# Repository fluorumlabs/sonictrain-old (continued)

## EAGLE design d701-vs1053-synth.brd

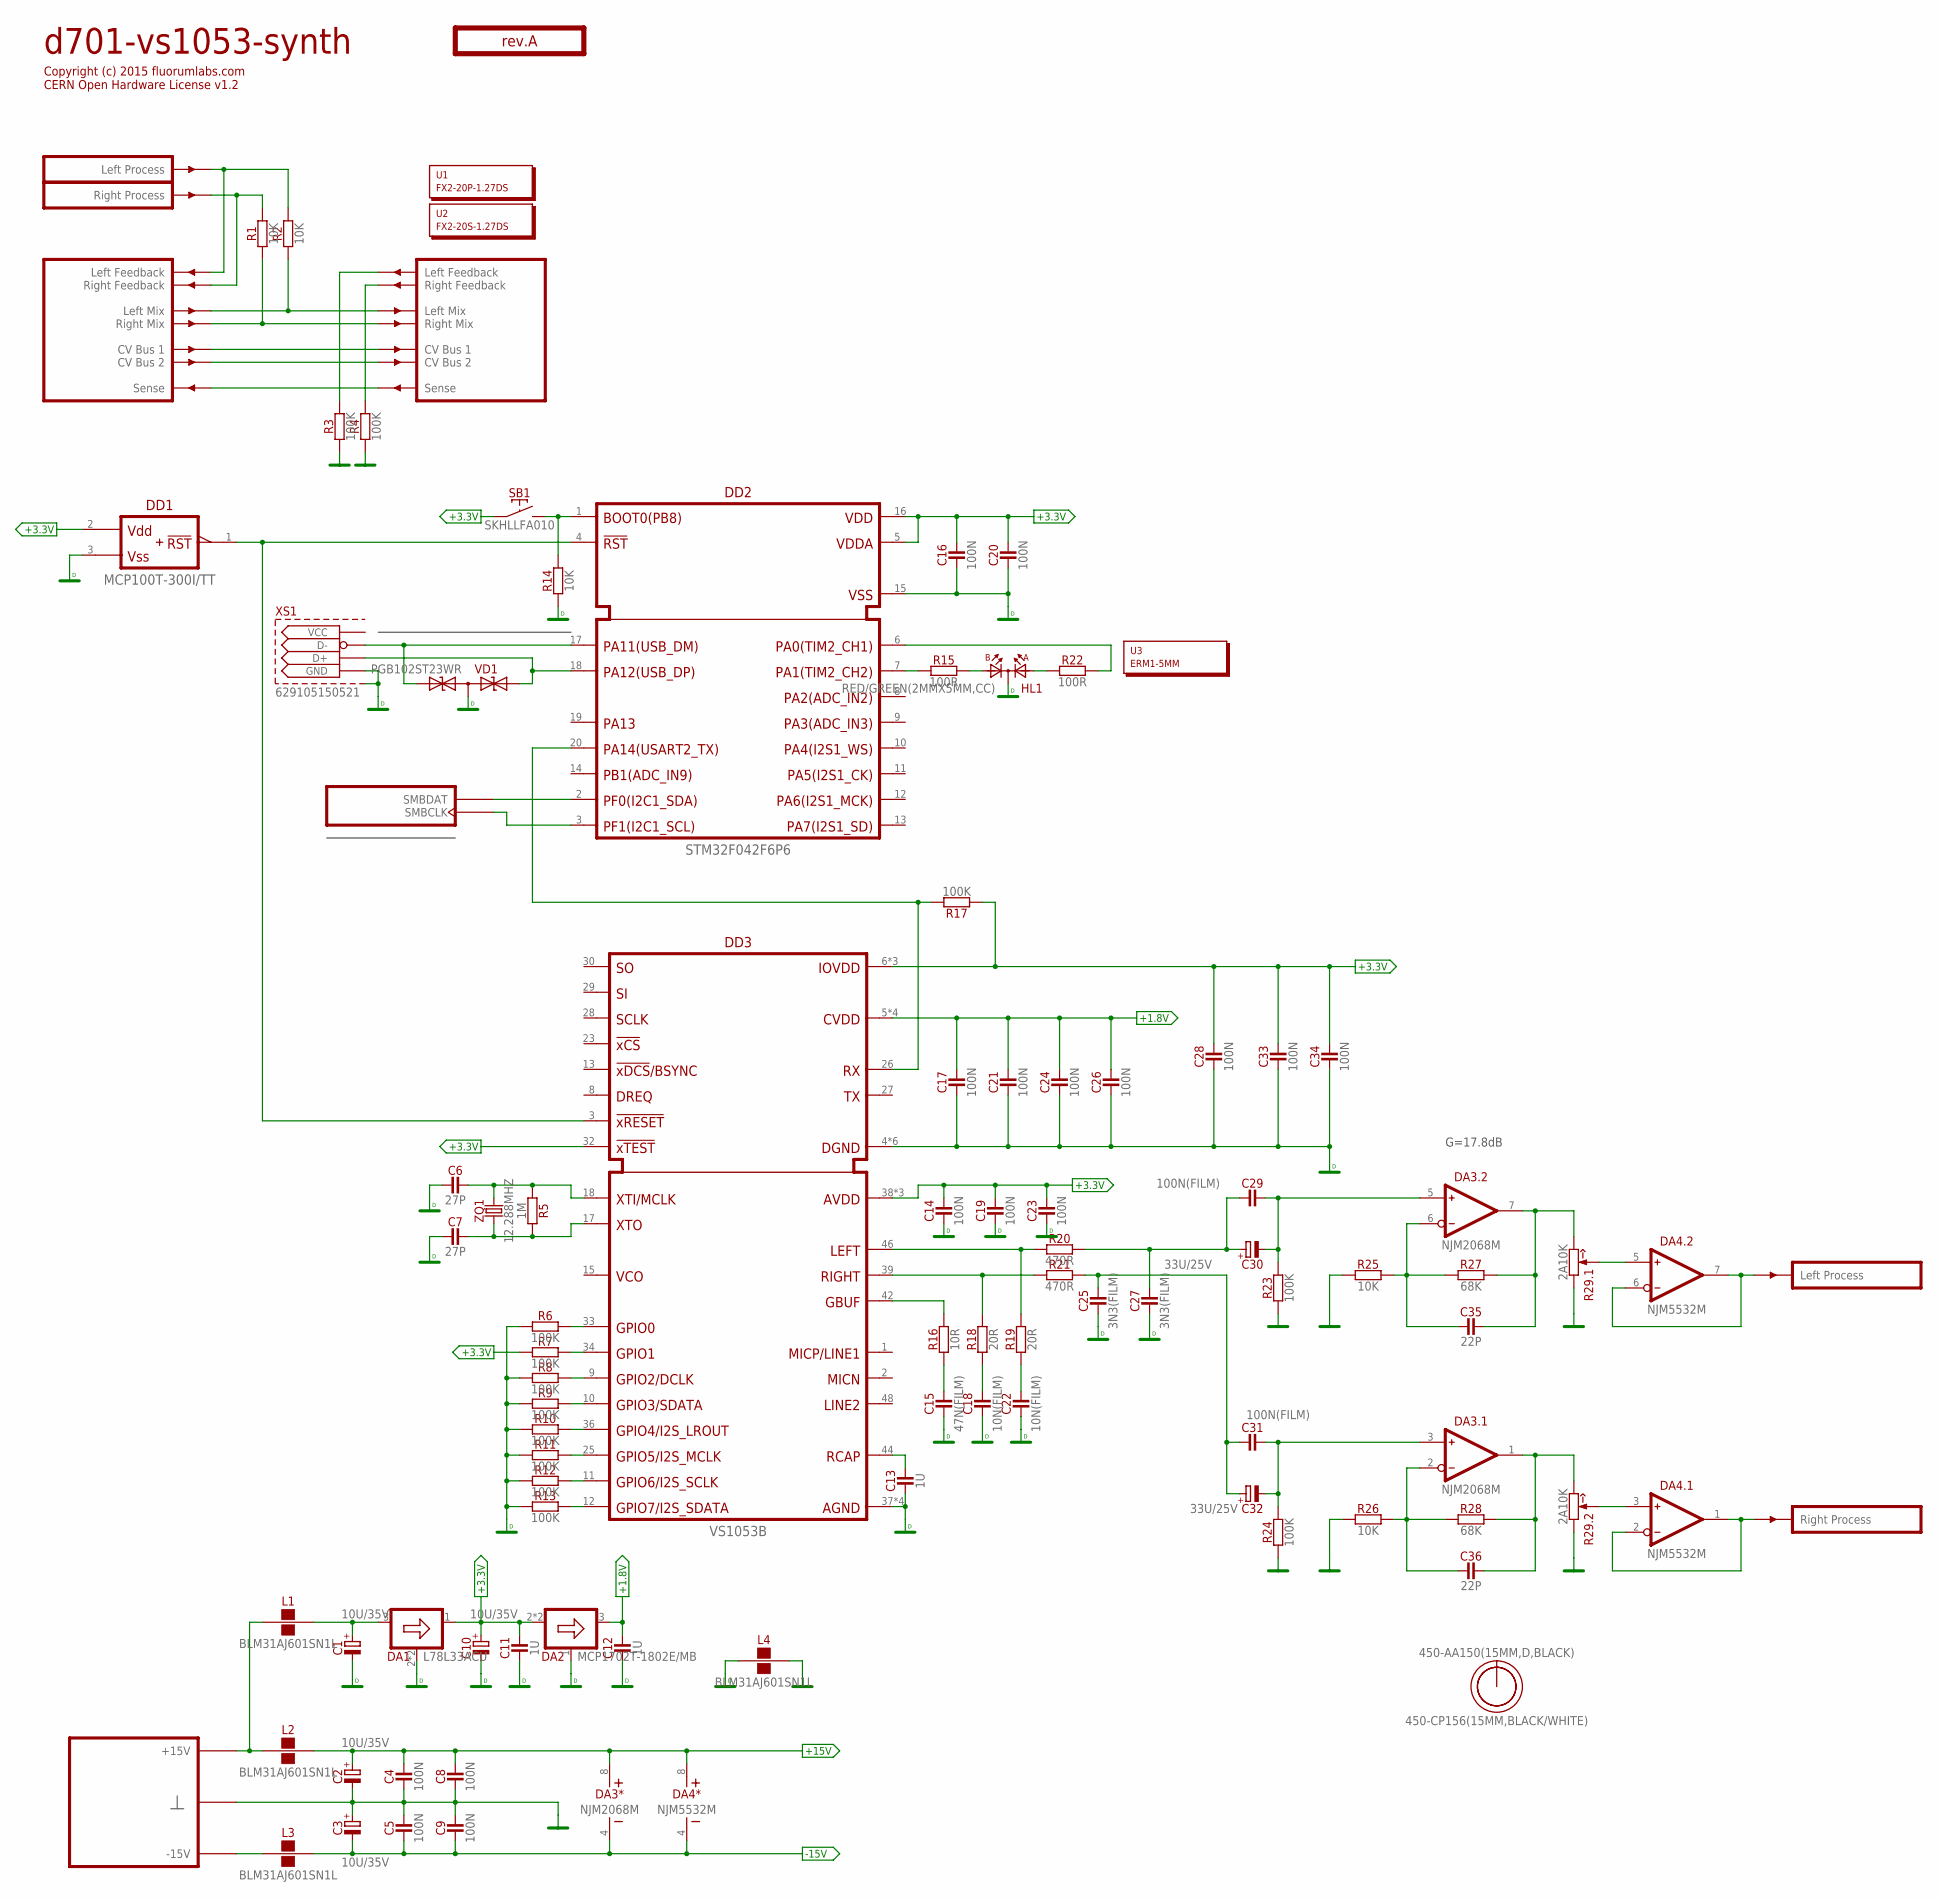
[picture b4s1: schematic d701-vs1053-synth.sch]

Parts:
C1, C2, C3, C10: 10U/35V; E2-5
C4, C5, C8, C9, C14, C16, C17, C19, C20, C21, C23, C24, C26, C28, C33, C34: 100N; C-0805
C6, C7: 27P; C-0805
C11, C12, C13: 1U; C-0805
C15: 47N(FILM); C050-025X075
C18, C22: 10N(FILM); C050-025X075
C25, C27: 3N3(FILM); C050-025X075
C29, C31: 100N(FILM); C050-025X075
C30, C32: 33U/25V; E2,5-7
C35, C36: 22P; C-0805
DA1: L78L33ACU; SOT89
DA2: MCP1702T-1802E/MB; SOT89
DA3: NJM2068M; SO-8
DA4: NJM5532M; SO-8
DD1: MCP100T-300I/TT; SOT23
DD2: STM32F042F6P6; TSSOP20
DD3: VS1053B; LQFP48-7X7
HL1: RED/GREEN(2MMX5MM,CC); LED2X5-3PIN
L1, L2, L3, L4: BLM31AJ601SN1L; 1206
O1: TITLE; EMPTY
O2: 450-AA150(15MM,D,BLACK); EMPTY
O3: 450-CP156(15MM,BLACK/WHITE); EMPTY
PCB1: rev.A; ST2-BOARD-50
R1, R2, R14, R25, R26: 10K; R-0805
R3, R4, R6, R7, R8, R9, R10, R11, R12, R13, R17, R23, R24: 100K; R-0805
R5: 1M; R-0805
R15, R22: 100R; R-0805
R16: 10R; R-0805
R18, R19: 20R; R-0805
R20, R21: 470R; R-0805
R27, R28: 68K; R-0805
R29: 2A10K; RV11-DUAL
SB1: SKHLLFA010
U1: FX2-20P-1.27DS; EMPTY
U2: FX2-20S-1.27DS; EMPTY
U3: ERM1-5MM; EMPTY
VD1: PGB102ST23WR; SOT23
XS1: 629105150521; MICROUSB-WURTH
ZQ1: 12.288MHZ; 3225

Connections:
+1.8V: C12.2, C17.2, C21.2, C24.2, C26.2, DA2.3 (OUT), DD3.5 (CVDD), DD3.7 (CVDD), DD3.24 (CVDD), DD3.31 (CVDD)
+3.3V: C10.+, C11.2, C14.2, C16.2, C19.2, C20.2, C23.2, C28.2, C33.2, C34.2, DA1.1 (OUT), DA2.2 (IN), DA2.2@1 (IN), DD1.2 (VDD), DD2.5 (VDDA), DD2.16 (VDD), DD3.6 (IOVDD), DD3.14 (IOVDD), DD3.19 (IOVDD), DD3.32 (!XTEST), DD3.38 (AVDD), DD3.43 (AVDD), DD3.45 (AVDD), R7.1, R17.1, SB1.1
+15V: C2.+, C4.2, C8.2, DA3.8 (V+), DA4.8 (V+), L2.2
-15V: C3.-, C5.1, C9.1, DA3.4 (V-), DA4.4 (V-), L3.2
DGND: C1.-, C6.1, C7.1, C10.-, C11.1, C12.1, C13.1, C14.1, C15.1, C16.1, C17.1, C18.1, C19.1, C20.1, C21.1, C22.1, C23.1, C24.1, C25.1, C26.1, C27.1, C28.1, C33.1, C34.1, DA1.2 (GND), DA1.2@1 (GND), DA2.1 (GND), DD1.3 (VSS), DD2.15 (VSS), DD3.4 (DGND), DD3.16 (DGND), DD3.20 (DGND), DD3.21 (DGND), DD3.22 (DGND), DD3.35 (DGND), DD3.37 (AGND), DD3.40 (AGND), DD3.41 (AGND), DD3.47 (AGND), HL1.K, L4.1, R6.1, R8.1, R9.1, R10.1, R11.1, R12.1, R13.1, R14.1, VD1.3 (C), XS1.5 (GND), XS1.S1, XS1.S2 (S1), XS1.S3 (S1), XS1.S4 (S1), XS1.S5 (S1), XS1.S6 (S1)
GND: C2.-, C3.+, C4.1, C5.2, C8.1, C9.2, L4.2, PCB1.B4 (GND), PCB1.B4' (GND), PCB1.B5 (GND), PCB1.B5' (GND), PCB1.B6 (GND), PCB1.B6' (GND), PCB1.B7 (GND), PCB1.B7' (GND), PCB1.B8 (GND), PCB1.B8' (GND), R3.1, R4.1, R23.1, R24.1, R25.1, R26.1, R29.1 (CCW), R29.1' (CCW)
LMIX: PCB1.ALMIX (LMIX), PCB1.ALMIX' (LMIX'), R2.1
unnamed: L1.1, L2.1, PCB1.A+15 (P+15V), PCB1.A+15' (P+15V), PCB1.B+15 (P+15V), PCB1.B+15' (P+15V)
unnamed: PCB1.ARFBK' (RFBK'), R4.2
unnamed: PCB1.ALFBK' (LFBK'), R3.2
unnamed: L3.1, PCB1.A-15 (P-15V), PCB1.A-15' (P-15V), PCB1.B-15 (P-15V), PCB1.B-15' (P-15V)
unnamed: C27.2, C29.1, C30.+, R20.2
unnamed: C31.2, C32.-, DA3.3 (IN+), R24.2
unnamed: C29.2, C30.-, DA3.5 (IN+), R23.2
unnamed: C36.2, DA3.1 (OUT), R28.2, R29.3' (CW)
unnamed: C35.2, DA3.7 (OUT), R27.2, R29.3 (CW)
unnamed: C35.1, DA3.6 (IN-), R25.2, R27.1
unnamed: C36.1, DA3.2 (IN-), R26.2, R28.1
unnamed: PCB1.BSENSE (SENSE), PCB1.BSENSE' (SENSE')
unnamed: C7.2, DD3.17 (XTO), R5.2, ZQ1.1
unnamed: DA4.6 (IN-), DA4.7 (OUT), PCB1.BOUTL' (OUTL)
unnamed: DA4.1 (OUT), DA4.2 (IN-), PCB1.BOUTR' (OUTR)
unnamed: DA4.5 (IN+), R29.2 (W)
unnamed: DA4.3 (IN+), R29.2' (W)
unnamed: C1.+, DA1.3 (IN), L1.2
unnamed: C6.2, DD3.18 (XTI/MCLK), R5.1, ZQ1.3 (2)
unnamed: C25.2, C31.1, C32.+, R21.2
unnamed: PCB1.ARFBK (RFBK), PCB1.BINR (INR), R1.2
unnamed: PCB1.ALFBK (LFBK), PCB1.BINL (INL), R2.2
unnamed: PCB1.ACV1 (CV1), PCB1.ACV1' (CV1')
unnamed: PCB1.ACV2 (CV2), PCB1.ACV2' (CV2')
unnamed: DD1.1 (!RST), DD2.4 (!RST), DD3.3 (!XRESET)
unnamed: DD3.12 (GPIO7/I2S_SDATA), R13.2
unnamed: DD3.11 (GPIO6/I2S_SCLK), R12.2
unnamed: DD3.25 (GPIO5/I2S_MCLK), R11.2
unnamed: DD2.20 (PA14), DD3.26 (RX), R17.2
unnamed: DD3.36 (GPIO4/I2S_LROUT), R10.2
unnamed: DD3.10 (GPIO3/SDATA), R9.2
unnamed: DD3.9 (GPIO2/DCLK), R8.2
unnamed: DD3.34 (GPIO1), R7.2
unnamed: DD3.33 (GPIO0), R6.2
unnamed: C13.2, DD3.44 (RCAP)
unnamed: DD2.7 (PA1), R15.1
unnamed: C15.2, R16.1
unnamed: HL1.A2, R15.2
unnamed: DD3.42 (GBUF), R16.2
unnamed: DD3.39 (RIGHT), R18.2, R21.1
unnamed: C18.2, R18.1
unnamed: DD3.46 (LEFT), R19.2, R20.1
unnamed: C22.2, R19.1
unnamed: HL1.A1, R22.1
unnamed: DD2.6 (PA0), R22.2
unnamed: DD2.1 (BOOT0), R14.2, SB1.2
RMIX: PCB1.ARMIX (RMIX), PCB1.ARMIX' (RMIX'), R1.1
SMBCLK: DD2.3 (PF1), PCB1.ASMBCLK (SMBCLK), PCB1.ASMBCLK' (SMBCLK)
SMBDAT: DD2.2 (PF0), PCB1.ASMBDAT (SMBDAT), PCB1.ASMBDAT' (SMBDAT)
USB_N: DD2.17 (PA11), VD1.2 (A1), XS1.2 (D-)
USB_P: DD2.18 (PA12), VD1.1 (A), XS1.3 (D+)

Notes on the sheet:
G=17.8dB

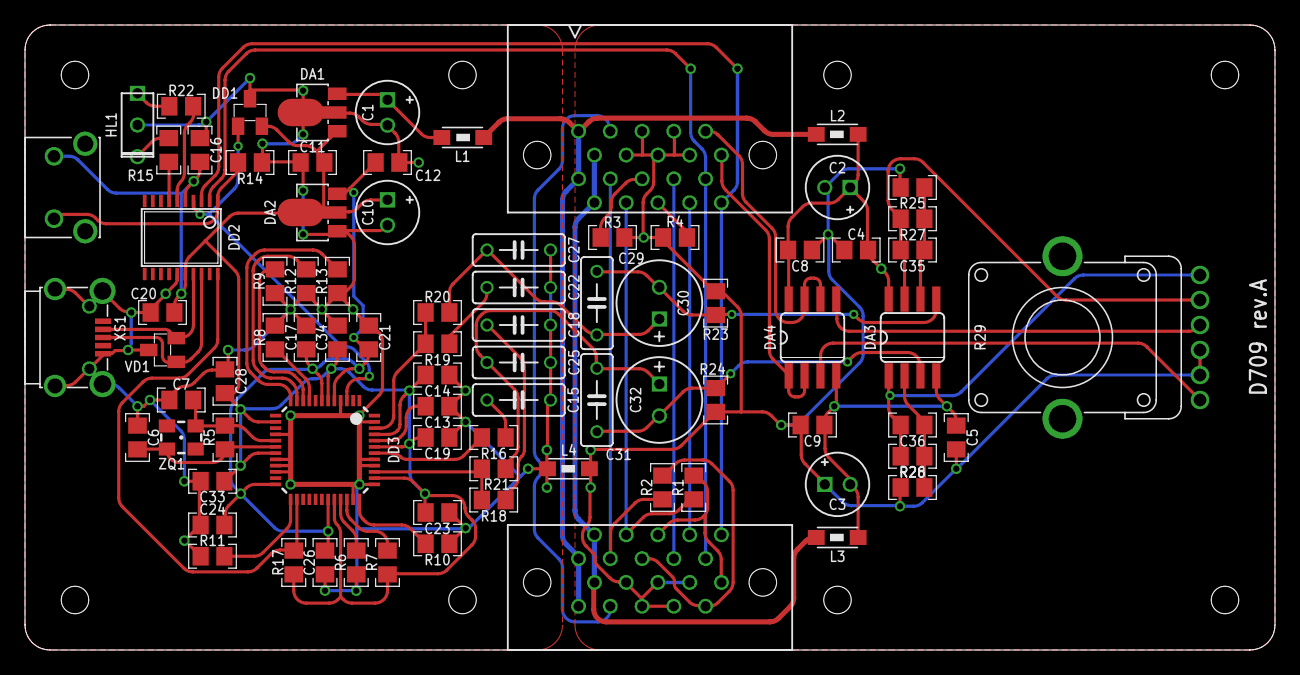
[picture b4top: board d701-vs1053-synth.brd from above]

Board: 2 copper layers, 100.0 x 50.0 mm, 95 parts (0 on the bottom side), 58 nets.

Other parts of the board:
U4, U5, U6, U7: SCREW-M2X8; EMPTY
U8, U9, U10, U11: NUT-M2-SELFLOCK; EMPTY

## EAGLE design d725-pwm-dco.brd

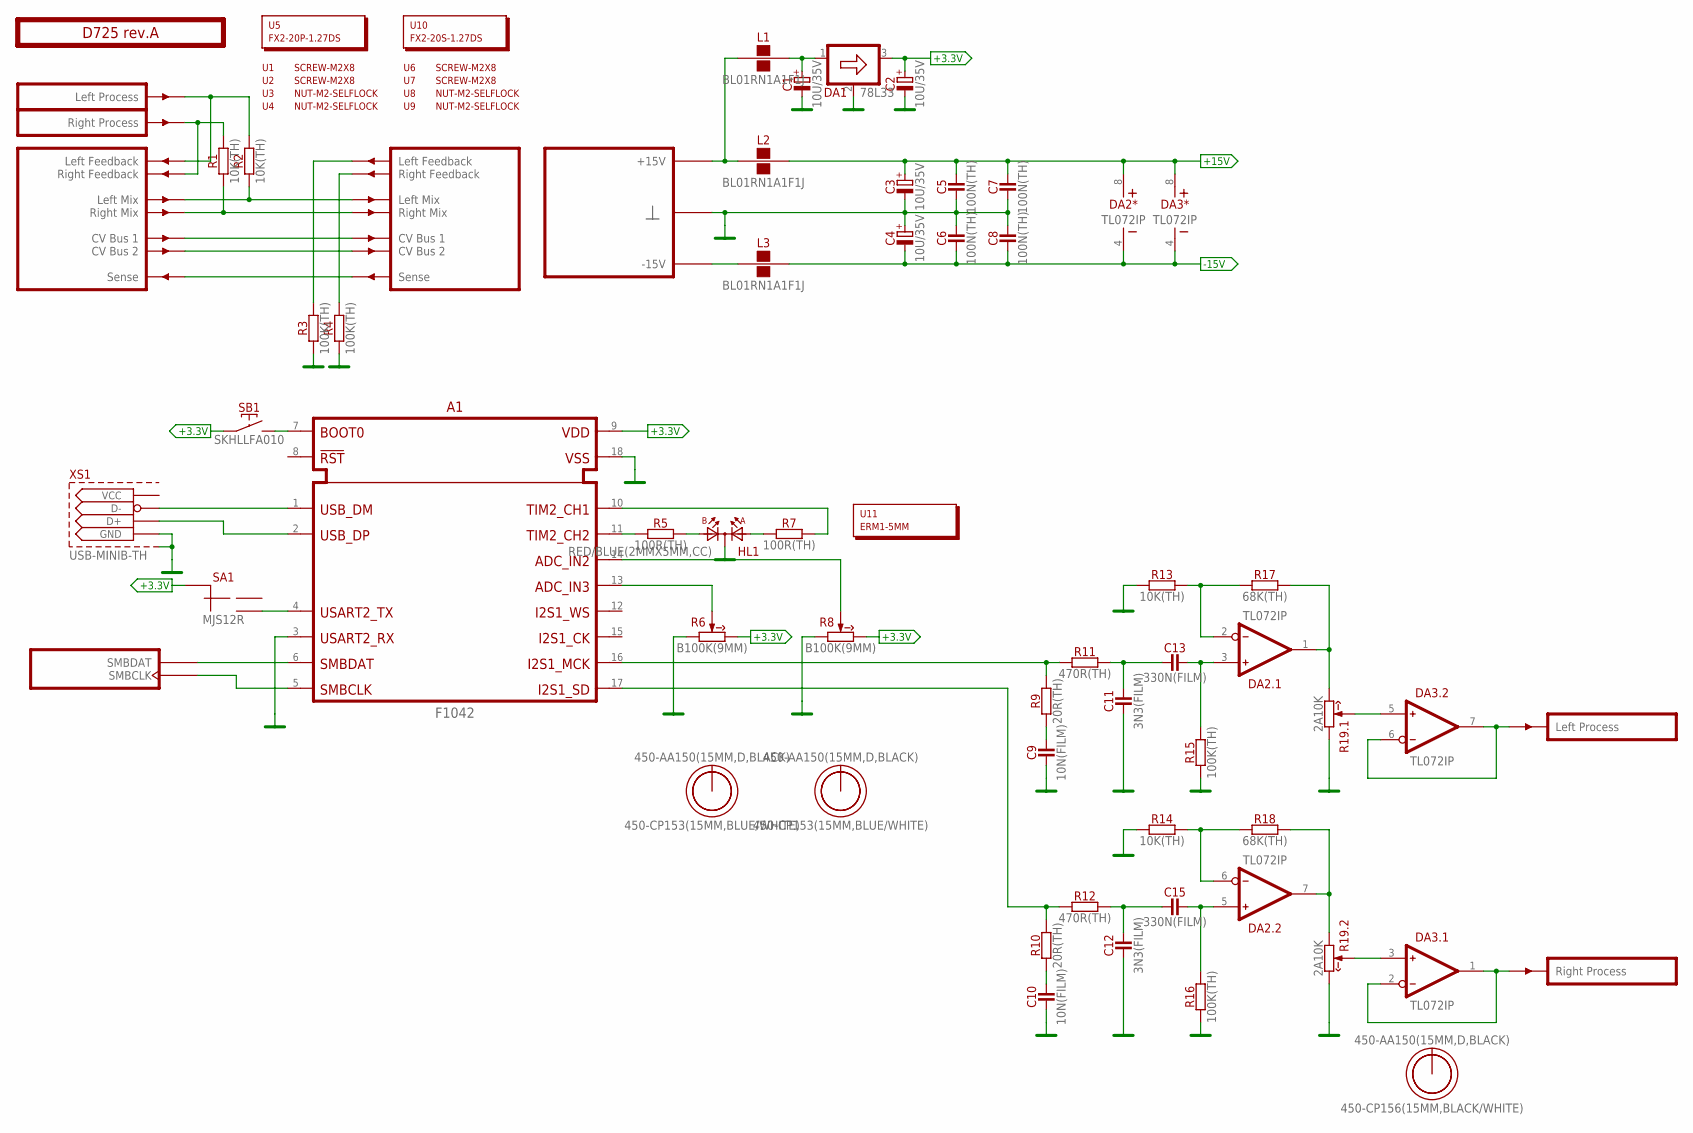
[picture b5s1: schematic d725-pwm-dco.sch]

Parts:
A1: F1042; F-DIP18
C1, C2, C3, C4: 10U/35V; E2-5
C5, C6, C7, C8: 100N(TH); C050-024X044
C9, C10: 10N(FILM); C050-025X075
C11, C12: 3N3(FILM); C050-025X075
C13, C15: 330N(FILM); C050-035X075
DA1: 78L33; TO92
DA2, DA3: TL072IP; DIP-8
HL1: RED/BLUE(2MMX5MM,CC); LED2X5-3PIN
L1, L2, L3: BL01RN1A1F1J; BL01RN1A
O1, O3, O5: 450-AA150(15MM,D,BLACK); EMPTY
O2, O4: 450-CP153(15MM,BLUE/WHITE); EMPTY
O6: 450-CP156(15MM,BLACK/WHITE); EMPTY
PCB1: D725 rev.A; ST2-BOARD-50
R1, R2, R13, R14: 10K(TH); R-0207/10
R3, R4, R15, R16: 100K(TH); R-0207/10
R5, R7: 100R(TH); R-0207/10
R6, R8: B100K(9MM); RV09-SINGLE
R9, R10: 20R(TH); R-0207/10
R11, R12: 470R(TH); R-0207/10
R17, R18: 68K(TH); R-0207/10
R19: 2A10K; RV11-DUAL
SA1: MJS12R; APEM-MJS12R
SB1: SKHLLFA010
U1, U2, U6, U7: SCREW-M2X8; EMPTY
U3, U4, U8, U9: NUT-M2-SELFLOCK; EMPTY
U5: FX2-20P-1.27DS; EMPTY
U10: FX2-20S-1.27DS; EMPTY
U11: ERM1-5MM; EMPTY
XS1: USB-MINIB-TH; USB-MB-H

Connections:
+3.3V: A1.9 (VDD), C2.+, DA1.3 (OUT), R6.3 (CW), R8.3 (CW), SA1.C (CM), SB1.1
+15V: C3.+, C5.2, C7.2, DA2.8 (V+), DA3.8 (V+), L2.2
-15V: C4.-, C6.1, C8.1, DA2.4 (V-), DA3.4 (V-), L3.2
GND: A1.3 (USART2_RX), A1.18 (VSS), C1.-, C2.-, C3.-, C4.+, C5.1, C6.2, C7.1, C8.2, C9.1, C10.1, C11.1, C12.1, DA1.2 (GND), HL1.K, PCB1.B4 (GND), PCB1.B4' (GND), PCB1.B5 (GND), PCB1.B5' (GND), PCB1.B6 (GND), PCB1.B6' (GND), PCB1.B7 (GND), PCB1.B7' (GND), PCB1.B8 (GND), PCB1.B8' (GND), R3.1, R4.1, R6.1 (CCW), R8.1 (CCW), R13.1, R14.1, R15.1, R16.1, R19.1 (CCW), R19.3' (CW), XS1.GND, XS1.P$1 (S1), XS1.P$2 (S1), XS1.P$6 (S1), XS1.P$7 (S1)
LMIX: PCB1.ALMIX (LMIX), PCB1.ALMIX' (LMIX'), R2.1
unnamed: L1.1, L2.1, PCB1.A+15 (P+15V), PCB1.A+15' (P+15V), PCB1.B+15 (P+15V), PCB1.B+15' (P+15V)
unnamed: PCB1.ARFBK (RFBK), PCB1.BINR (INR), R1.2
unnamed: C1.+, DA1.1 (IN), L1.2
unnamed: PCB1.ALFBK (LFBK), PCB1.BINL (INL), R2.2
unnamed: A1.11 (TIM2_CH2), R5.1
unnamed: A1.6 (SBMDAT), PCB1.ASMBDAT (SMBDAT), PCB1.ASMBDAT' (SMBDAT)
unnamed: A1.5 (SMBCLK), PCB1.ASMBCLK (SMBCLK), PCB1.ASMBCLK' (SMBCLK)
unnamed: A1.7 (BOOT0), SB1.2
unnamed: A1.1 (USB_DM), XS1.D-
unnamed: C9.2, R9.1
unnamed: A1.16 (I2S1_MCK), R9.2, R11.1
unnamed: A1.2 (USB_DP), XS1.D+
unnamed: HL1.A2, R5.2
unnamed: HL1.A1, R7.1
unnamed: A1.10 (TIM2_CH1), R7.2
unnamed: PCB1.BSENSE (SENSE), PCB1.BSENSE' (SENSE')
unnamed: PCB1.ACV1 (CV1), PCB1.ACV1' (CV1')
unnamed: PCB1.ARFBK' (RFBK'), R4.2
unnamed: A1.13 (ADC_IN3), R6.2 (W)
unnamed: A1.14 (ADC_IN2), R8.2 (W)
unnamed: PCB1.ALFBK' (LFBK'), R3.2
unnamed: PCB1.ACV2 (CV2), PCB1.ACV2' (CV2')
unnamed: A1.4 (USART2_TX), SA1.NO (2)
unnamed: L3.1, PCB1.A-15 (P-15V), PCB1.A-15' (P-15V), PCB1.B-15 (P-15V), PCB1.B-15' (P-15V)
unnamed: C10.2, R10.1
unnamed: A1.17 (I2S1_SD), R10.2, R12.1
unnamed: C12.2, C15.1, R12.2
unnamed: C15.2, DA2.5 (IN+), R16.2
unnamed: C11.2, C13.1, R11.2
unnamed: DA2.6 (IN-), R14.2, R18.1
unnamed: DA2.7 (OUT), R18.2, R19.1' (CCW)
unnamed: DA3.3 (IN+), R19.2' (W)
unnamed: DA3.1 (OUT), DA3.2 (IN-), PCB1.BOUTR' (OUTR)
unnamed: C13.2, DA2.3 (IN+), R15.2
unnamed: DA2.2 (IN-), R13.2, R17.1
unnamed: DA2.1 (OUT), R17.2, R19.3 (CW)
unnamed: DA3.5 (IN+), R19.2 (W)
unnamed: DA3.6 (IN-), DA3.7 (OUT), PCB1.BOUTL' (OUTL)
RMIX: PCB1.ARMIX (RMIX), PCB1.ARMIX' (RMIX'), R1.1

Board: 2 copper layers, 62 parts (0 on the bottom side), 44 nets, no tracks yet.
